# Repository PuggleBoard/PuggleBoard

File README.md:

PuggleBoard
===

Note: The PuggleBoard project is no longer under active development as of 06/2016. For alternative low-cost electrophysiology options, please see <a href="http://github.com/rtxi/rtxi">RTXI</a> or <a href="http://github.com/open-ephys/">Open-Ephys</a>.

The [PuggleBoard] (http://puggleboard.com/) is an I/O interface that plugs into the BeagleBone Black's expansion headers and is controlled by <a href="https://github.com/PuggleBoard/PuggleDriver">PuggleDriver</a>.

To get started, please refer to the <a href="https://github.com/PuggleBoard/PuggleBoard/wiki">wiki</a>. If you encounter any trouble or have any questions, post them to the <a href="https://github.com/PuggleBoard/PuggleBoard/issues">issues section</a> and we'll help get you started.

Visit visit the <a href="http://puggleboard.com">Puggleboard</a> site for more information on Puggle and it's hardware/software components.

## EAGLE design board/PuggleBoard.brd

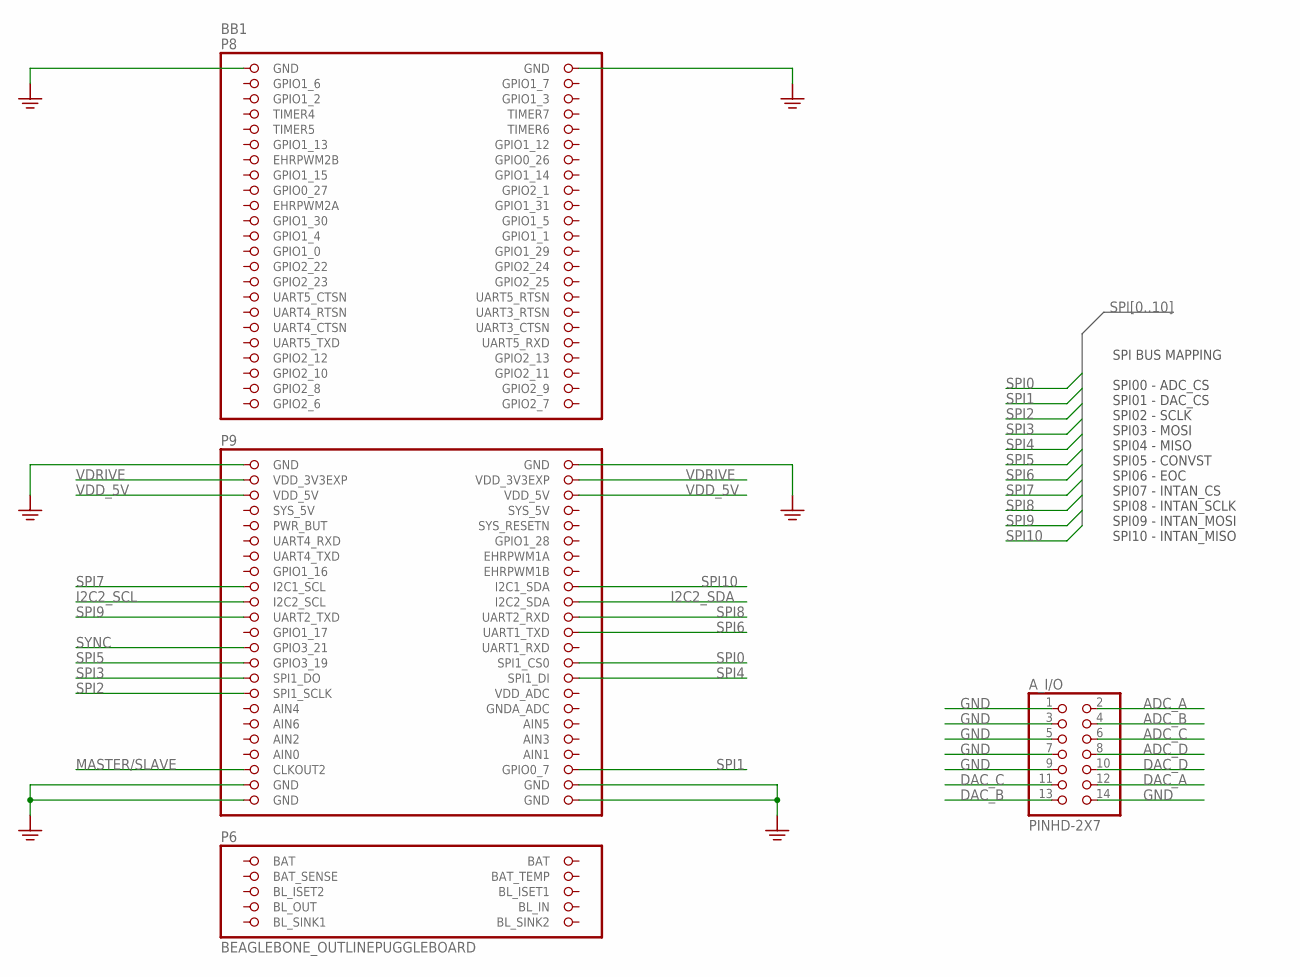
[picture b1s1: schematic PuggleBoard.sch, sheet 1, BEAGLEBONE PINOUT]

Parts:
A_I/O: PINHD-2X7; 2X07
BB1: BEAGLEBONE_OUTLINEPUGGLEBOARD; PUGGLEBOARD_SHIELD

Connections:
ADC_A: A_I/O.2; also elsewhere on the board
ADC_B: A_I/O.4; also elsewhere on the board
ADC_C: A_I/O.6; also elsewhere on the board
ADC_D: A_I/O.8; also elsewhere on the board
BAT_SENSE: BB1.95 (BAT_SENSE)
BL_IN: BB1.97 (BL_IN)
BL_OUT: BB1.100 (BL_OUT)
BL_SINK1: BB1.101 (BL_SINK1)
BL_SINK2: BB1.102 (BL_SINK2)
DAC_A: A_I/O.12; also elsewhere on the board
DAC_B: A_I/O.13; also elsewhere on the board
DAC_C: A_I/O.11; also elsewhere on the board
DAC_D: A_I/O.10; also elsewhere on the board
GND: A_I/O.1, A_I/O.3, A_I/O.5, A_I/O.7, A_I/O.9, A_I/O.14, BB1.1 (GND), BB1.2 (GND), BB1.47 (GND), BB1.48 (GND), BB1.89 (GND), BB1.90 (GND), BB1.91 (GND), BB1.92 (GND); also elsewhere on the board
I2C2_SCL: BB1.65 (I2C2_SCL); also elsewhere on the board
I2C2_SDA: BB1.66 (I2C2_SDA); also elsewhere on the board
MASTER/SLAVE: BB1.87 (CLKOUT2); also elsewhere on the board
SPI0: BB1.74 (SPI1_CS0); also elsewhere on the board
SPI1: BB1.88 (GPIO0_7); also elsewhere on the board
SPI2: BB1.77 (SPI1_SCLK); also elsewhere on the board
SPI3: BB1.75 (SPI1_DO); also elsewhere on the board
SPI4: BB1.76 (SPI1_DI); also elsewhere on the board
SPI5: BB1.73 (GPIO3_19); also elsewhere on the board
SPI6: BB1.70 (UART1_TXD); also elsewhere on the board
SPI7: BB1.63 (I2C1_SCL); also elsewhere on the board
SPI8: BB1.68 (UART2_RXD); also elsewhere on the board
SPI9: BB1.67 (UART2_TXD); also elsewhere on the board
SPI10: BB1.64 (I2C1_SDA); also elsewhere on the board
SYNC: BB1.71 (GPIO3_21); also elsewhere on the board
VDD_5V: BB1.51 (VDD_5V), BB1.52 (VDD_5V); also elsewhere on the board
VDRIVE: BB1.49 (VDD_3V3EXP), BB1.50 (VDD_3V3EXP); also elsewhere on the board

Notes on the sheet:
SPI BUS MAPPING SPI00 - ADC_CS SPI01 - DAC_CS SPI02 - SCLK SPI03 - MOSI SPI04 - MISO SPI05 - CONVST SPI06 - EOC SPI07 - INTAN_CS SPI08 - INTAN_SCLK SPI09 - INTAN_MOSI SPI10 - INTAN_MISO

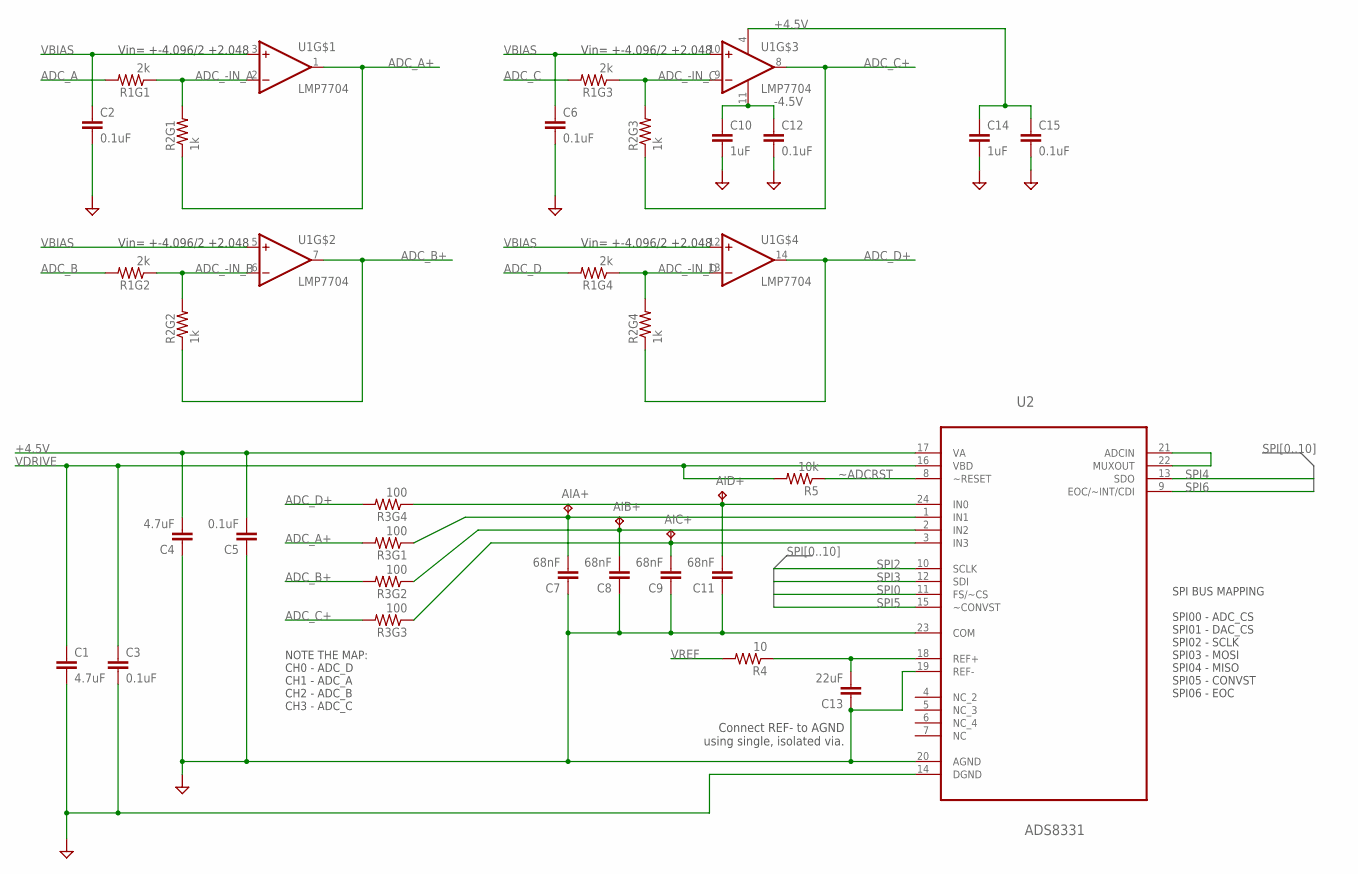
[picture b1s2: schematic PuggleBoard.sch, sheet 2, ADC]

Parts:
AIA+: TPB1,27; B1,27
AIB+: TPB1,27; B1,27
AIC+: TPB1,27; B1,27
AID+: TPB1,27; B1,27
C1, C4: 4.7uF; 0603
C2, C3, C5, C6, C12, C15: 0.1uF; 0603
C7, C8, C9, C11: 68nF; 0603
C10, C14: 1uF; 0603
C13: 22uF; 0805
R1: 2k; RX4_0612
R2: 1k; RX4_0612
R3: 100; RX4_0612
R4: 10; 0603
R5: 10k; 0603
U1: LMP7704; SOP65P640X120-14N-MOD
U2: ADS8331; SOP65P640X120-24N

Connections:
+4.5V: C4.2, C5.2, C14.1, C15.1, U1.4 (V+), U2.17 (VA); also elsewhere on the board
-4.5V: C10.1, C12.1, U1.11 (V-); also elsewhere on the board
ADC_-IN_A: R1.P1 (1), R2.P2 (2), U1.2 (-IN)
ADC_-IN_B: R1.P3 (1), R2.P4 (2), U1.6 (-IN)
ADC_-IN_C: R1.P5 (1), R2.P6 (2), U1.9 (-IN)
ADC_-IN_D: R1.P7 (1), R2.P8 (2), U1.13 (-IN)
ADC_A: R1.P2 (2); also elsewhere on the board
ADC_A+: R2.P1 (1), R3.P2 (2), U1.1 (OUT)
ADC_B: R1.P4 (2); also elsewhere on the board
ADC_B+: R2.P3 (1), R3.P4 (2), U1.7 (OUT)
ADC_C: R1.P6 (2); also elsewhere on the board
ADC_C+: R2.P5 (1), R3.P6 (2), U1.8 (OUT)
ADC_D: R1.P8 (2); also elsewhere on the board
ADC_D+: R2.P7 (1), R3.P8 (2), U1.14 (OUT)
GND: C1.2, C2.2, C3.2, C4.1, C5.1, C6.2, C7.1, C8.1, C9.1, C10.2, C11.1, C12.2, C13.1, C14.2, C15.2, U2.14 (DGND), U2.19 (REF-), U2.20 (AGND), U2.23 (COM); also elsewhere on the board
unnamed: U2.21 (ADCIN), U2.22 (MUXOUT)
unnamed: C13.2, R4.1, U2.18 (REF+)
unnamed: AIA+.TP, C7.2, R3.P1 (1), U2.1 (IN1)
unnamed: AIB+.TP, C8.2, R3.P3 (1), U2.2 (IN2)
unnamed: AIC+.TP, C9.2, R3.P5 (1), U2.3 (IN3)
unnamed: AID+.TP, C11.2, R3.P7 (1), U2.24 (IN0)
SPI0: U2.11 (FS/~CS); also elsewhere on the board
SPI2: U2.10 (SCLK); also elsewhere on the board
SPI3: U2.12 (SDI); also elsewhere on the board
SPI4: U2.13 (SDO); also elsewhere on the board
SPI5: U2.15 (~CONVST); also elsewhere on the board
SPI6: U2.9 (EOC/~INT/CDI); also elsewhere on the board
VBIAS: C2.1, C6.1, U1.3 (+IN), U1.5 (+IN), U1.10 (+IN), U1.12 (+IN); also elsewhere on the board
VDRIVE: C1.1, C3.1, R5.2, U2.16 (VBD); also elsewhere on the board
VREF: R4.2; also elsewhere on the board
~ADCRST: R5.1, U2.8 (~RESET)

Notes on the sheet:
Connect REF- to AGND using single, isolated via.
Vin= +-4.096/2 +2.048
SPI BUS MAPPING SPI00 - ADC_CS SPI01 - DAC_CS SPI02 - SCLK SPI03 - MOSI SPI04 - MISO SPI05 - CONVST SPI06 - EOC
NOTE THE MAP: CH0 - ADC_D CH1 - ADC_A CH2 - ADC_B CH3 - ADC_C

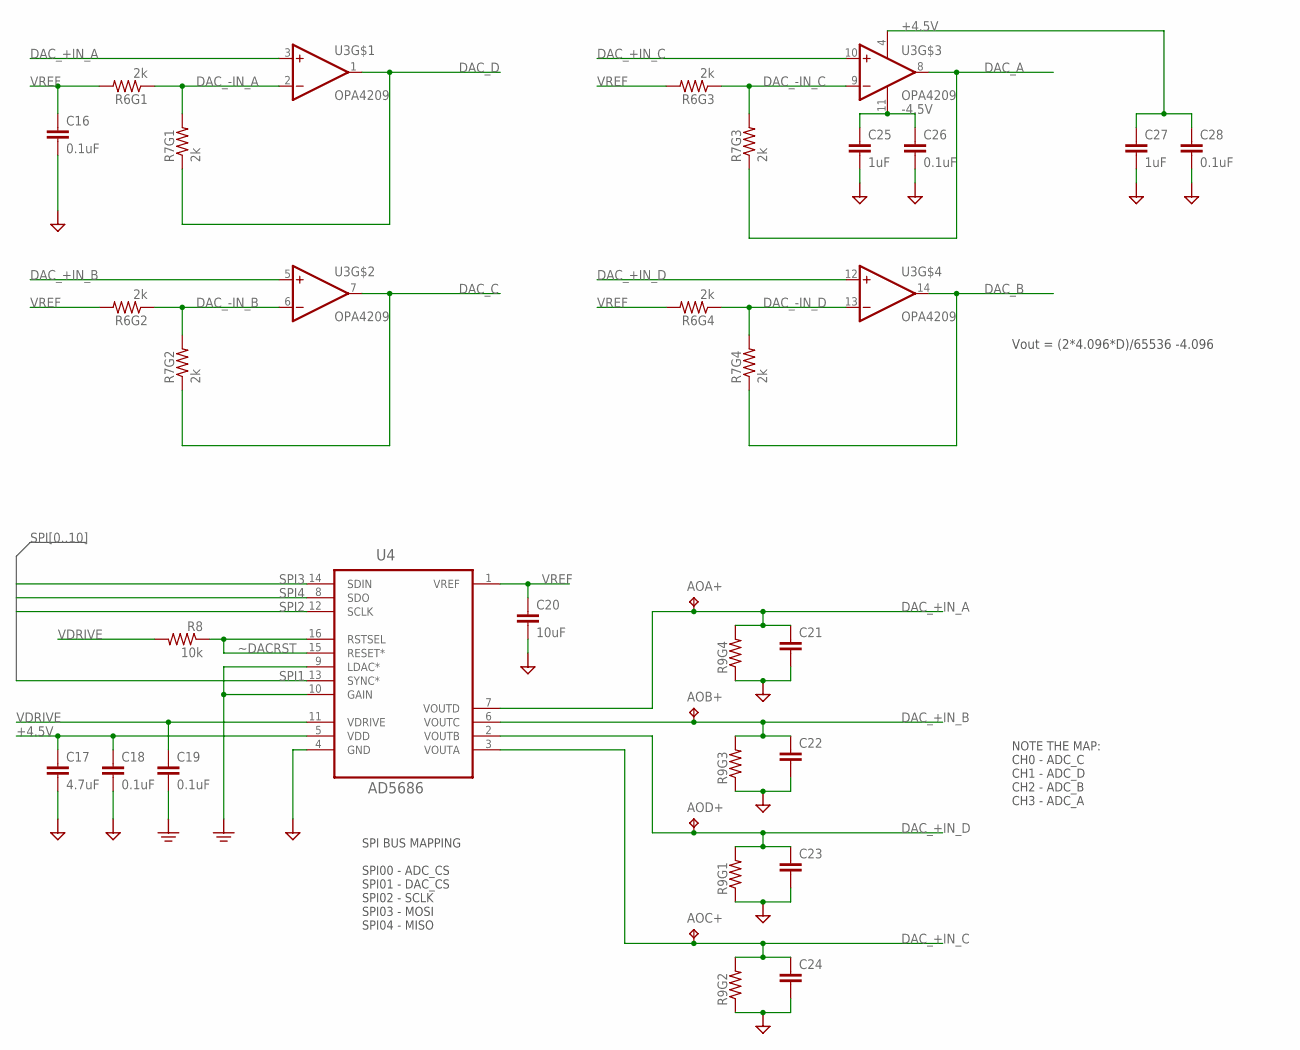
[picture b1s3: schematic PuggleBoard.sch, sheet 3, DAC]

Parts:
AOA+: TPB1,27; B1,27
AOB+: TPB1,27; B1,27
AOC+: TPB1,27; B1,27
AOD+: TPB1,27; B1,27
C16, C18, C19, C26, C28: 0.1uF; 0603
C17: 4.7uF; 0603
C20: 10uF; 0805
C21, C22, C23, C24: C_0603; 0603
C25, C27: 1uF; 0603
R6, R7: 2k; RX4_0612
R8: 10k; 0603
R9: RX4_0612
U3: OPA4209; SOP65P640X120-14N-MOD
U4: AD5686; MO-153-AB

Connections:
+4.5V: C17.1, C18.1, C27.1, C28.1, U3.4 (V+), U4.5 (VDD); also elsewhere on the board
-4.5V: C25.1, C26.1, U3.11 (V-); also elsewhere on the board
DAC_+IN_A: AOA+.TP, C21.1, R9.P8 (2), U3.3 (+IN), U4.7 (VOUTD)
DAC_+IN_B: AOB+.TP, C22.1, R9.P6 (2), U3.5 (+IN), U4.6 (VOUTC)
DAC_+IN_C: AOC+.TP, C24.1, R9.P4 (2), U3.10 (+IN), U4.3 (VOUTA)
DAC_+IN_D: AOD+.TP, C23.1, R9.P2 (2), U3.12 (+IN), U4.2 (VOUTB)
DAC_-IN_A: R6.P1 (1), R7.P2 (2), U3.2 (-IN)
DAC_-IN_B: R6.P3 (1), R7.P4 (2), U3.6 (-IN)
DAC_-IN_C: R6.P5 (1), R7.P6 (2), U3.9 (-IN)
DAC_-IN_D: R6.P7 (1), R7.P8 (2), U3.13 (-IN)
DAC_A: R7.P5 (1), U3.8 (OUT); also elsewhere on the board
DAC_B: R7.P7 (1), U3.14 (OUT); also elsewhere on the board
DAC_C: R7.P3 (1), U3.7 (OUT); also elsewhere on the board
DAC_D: R7.P1 (1), U3.1 (OUT); also elsewhere on the board
GND: C16.2, C17.2, C18.2, C19.2, C20.2, C21.2, C22.2, C23.2, C24.2, C25.2, C26.2, C27.2, C28.2, R9.P1 (1), R9.P3 (1), R9.P5 (1), R9.P7 (1), U4.4 (GND), U4.9 (LDAC*), U4.10 (GAIN); also elsewhere on the board
SPI1: U4.13 (SYNC*); also elsewhere on the board
SPI2: U4.12 (SCLK); also elsewhere on the board
SPI3: U4.14 (SDIN); also elsewhere on the board
SPI4: U4.8 (SDO); also elsewhere on the board
VDRIVE: C19.1, R8.2, U4.11 (VDRIVE); also elsewhere on the board
VREF: C16.1, C20.1, R6.P2 (2), R6.P4 (2), R6.P6 (2), R6.P8 (2), U4.1 (VREF); also elsewhere on the board
~DACRST: R8.1, U4.15 (RESET*), U4.16 (RSTSEL)

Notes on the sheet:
Vout = (2*4.096*D)/65536 -4.096
SPI BUS MAPPING SPI00 - ADC_CS SPI01 - DAC_CS SPI02 - SCLK SPI03 - MOSI SPI04 - MISO
NOTE THE MAP: CH0 - ADC_C CH1 - ADC_D CH2 - ADC_B CH3 - ADC_A

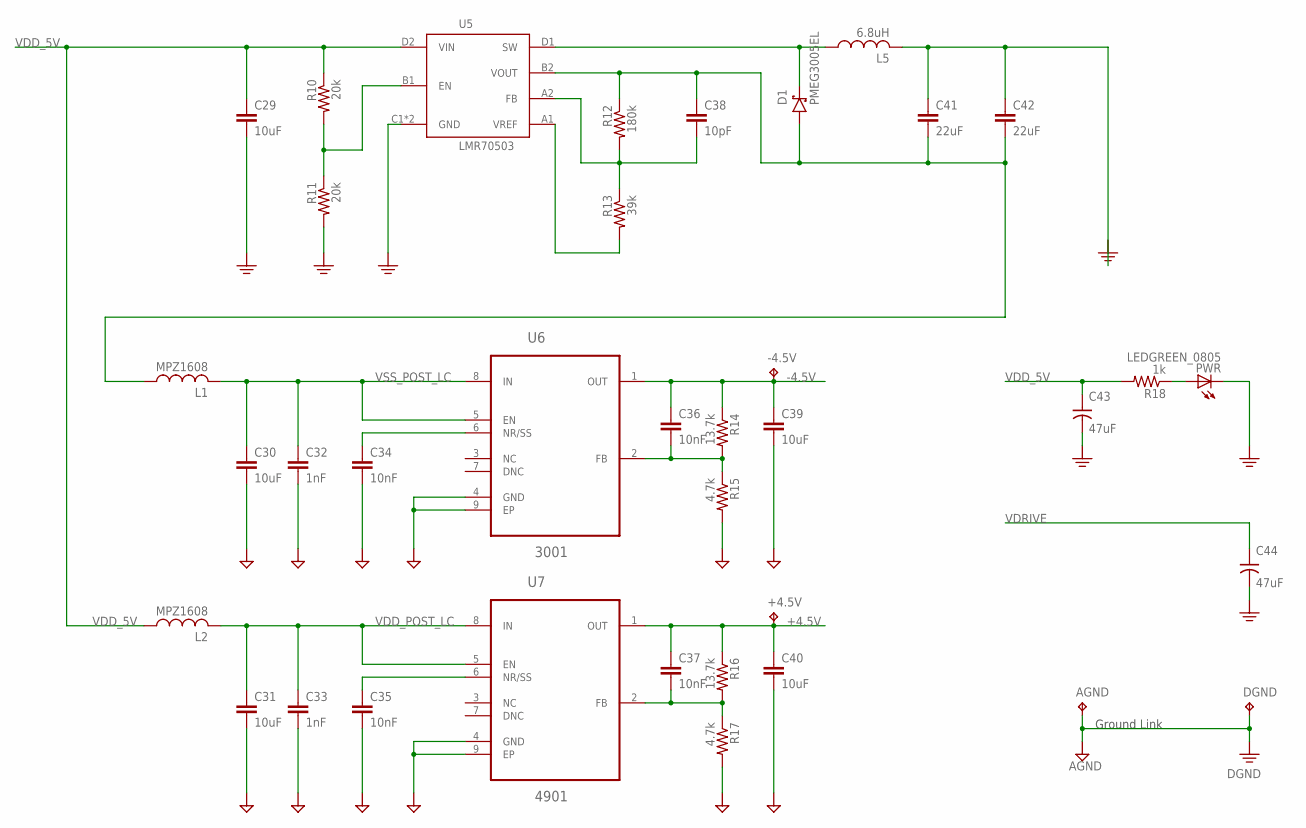
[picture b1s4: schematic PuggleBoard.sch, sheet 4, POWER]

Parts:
+4.5V: TPPAD1-17; P1-17
-4.5V: TPPAD1-17; P1-17
AGND: TPPAD1-17; P1-17
C29: 10uF; 0603
C30, C31, C39, C40: 10uF; 1206
C32, C33: 1nF; 0603
C34, C35, C36, C37: 10nF; 0603
C38: 10pF; 0402
C41, C42: 22uF; 0603
C43, C44: 47uF; 153CLV-0807
D1: PMEG3005EL; SOD882
DGND: TPPAD1-17; P1-17
L1, L2: MPZ1608; 0603
L5: 6.8uH; VLS2012E
PWR: LEDGREEN_0805; CHIP-LED0805
R10, R11: 20k; 0402
R12: 180k; 0402
R13: 39k; 0402
R14, R16: 13.7k; 0603
R15, R17: 4.7k; 0603
R18: 1k; 0603
U5: LMR70503; 8BGA
U6: 3001; SOP65P490X110-9N
U7: 4901; SOP65P490X110-9N

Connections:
+4.5V: +4.5V.TP, C37.1, C40.1, R16.1, U7.1 (OUT); also elsewhere on the board
-4.5V: -4.5V.TP, C36.1, C39.1, R14.1, U6.1 (OUT); also elsewhere on the board
AGND1: C37.2, R16.2, R17.1, U7.2 (FB)
AGND2: C36.2, R14.2, R15.1, U6.2 (FB)
GND: AGND.TP, C29.2, C30.2, C31.2, C32.2, C33.2, C34.2, C35.2, C39.2, C40.2, C41.1, C42.1, C43.-, C44.-, DGND.TP, L5.2, PWR.C, R11.2, R15.2, R17.2, U5.C1 (GND), U5.C2 (GND), U6.4 (GND), U6.9 (EP), U7.4 (GND), U7.9 (EP); also elsewhere on the board
unnamed: C35.1, U7.6 (NR/SS)
unnamed: C34.1, U6.6 (NR/SS)
unnamed: R10.2, R11.1, U5.B1 (EN)
unnamed: C38.2, R12.2, R13.1, U5.A2 (FB)
unnamed: PWR.A, R18.1
unnamed: R13.2, U5.A1 (VREF)
SW: D1.C, L5.1, U5.D1 (SW)
VDD_5V: C29.1, C43.+, L2.1, R10.1, R18.2, U5.D2 (VIN); also elsewhere on the board
VDD_POST_LC: C31.1, C33.1, L2.2, U7.5 (EN), U7.8 (IN)
VDRIVE: C44.+; also elsewhere on the board
VOUT-: C38.1, C41.2, C42.2, D1.A, L1.1, R12.1, U5.B2 (VOUT)
VSS_POST_LC: C30.1, C32.1, L1.2, U6.5 (EN), U6.8 (IN)

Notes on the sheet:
Ground Link

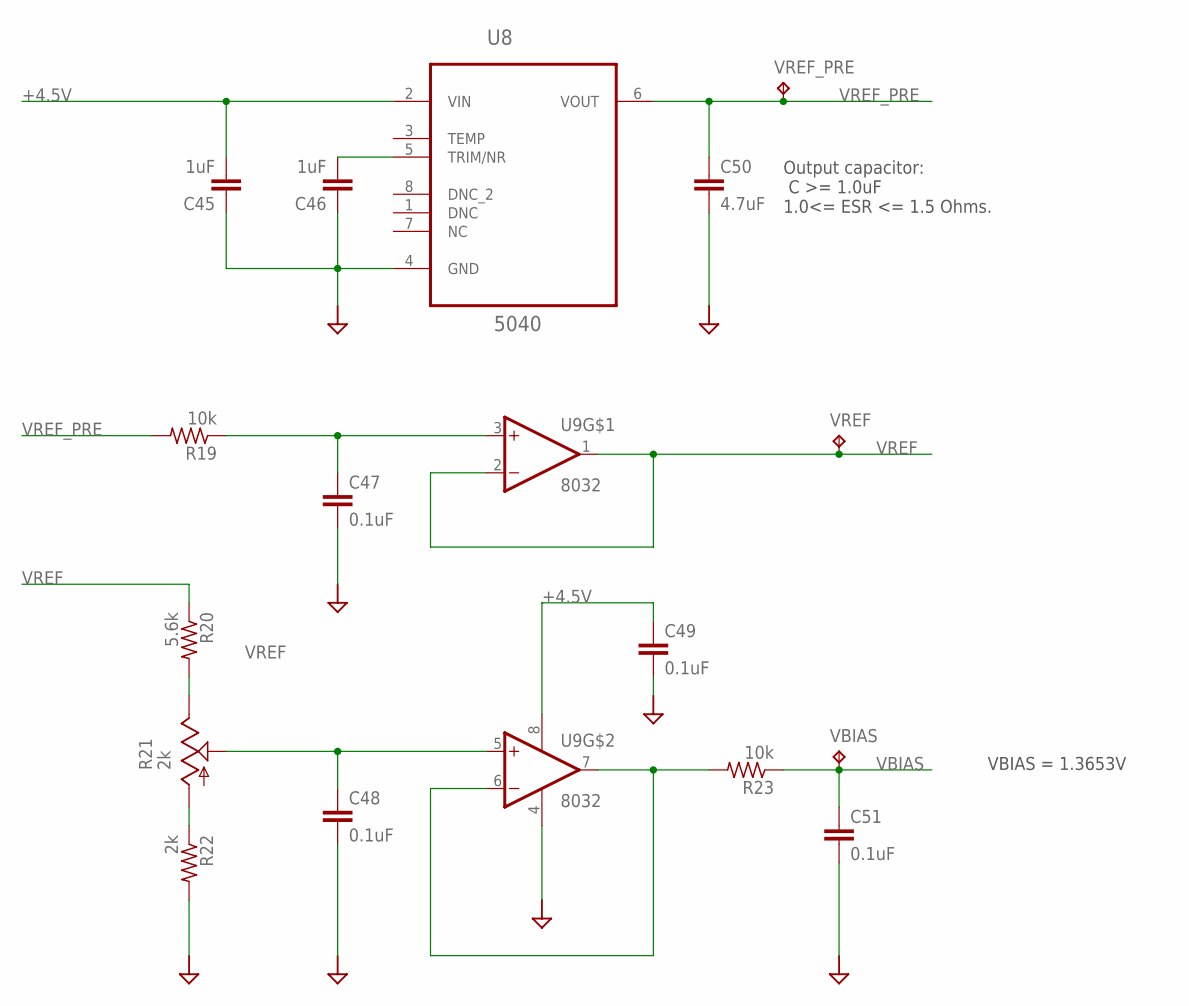
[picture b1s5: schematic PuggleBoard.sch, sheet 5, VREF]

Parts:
C45, C46: 1uF; 0603
C47, C48, C49, C51: 0.1uF; 0603
C50: 4.7uF; 1206
R19, R23: 10k; 0603
R20: 5.6k; 0603
R21: 2k; SM-42/43W
R22: 2k; 0603
U8: 5040; SOP65P490X110-8N
U9: 8032; SOP65P490X110-8N
VBIAS: TPB1,27; B1,27
VREF: TPB1,27; B1,27
VREF_PRE: TPB1,27; B1,27

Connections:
+4.5V: C45.2, C49.1, U8.2 (VIN), U9.8 (V+); also elsewhere on the board
GND: C45.1, C46.1, C47.2, C48.2, C49.2, C50.2, C51.2, R22.2, U8.4 (GND), U9.4 (V-); also elsewhere on the board
unnamed: C48.1, R21.2 (S), U9.5 (+IN)
unnamed: R21.1 (A), R22.1
unnamed: R23.2, U9.6 (-IN), U9.7 (OUT)
unnamed: R20.2, R21.3 (E)
unnamed: C47.1, R19.1, U9.3 (+IN)
unnamed: C46.2, U8.5 (TRIM/NR)
VBIAS: C51.1, R23.1, VBIAS.TP; also elsewhere on the board
VREF: R20.1, U9.1 (OUT), U9.2 (-IN), VREF.TP; also elsewhere on the board
VREF_PRE: C50.1, R19.2, U8.6 (VOUT), VREF_PRE.TP

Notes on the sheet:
Output capacitor: C >= 1.0uF 1.0<= ESR <= 1.5 Ohms.
VBIAS = 1.3653V

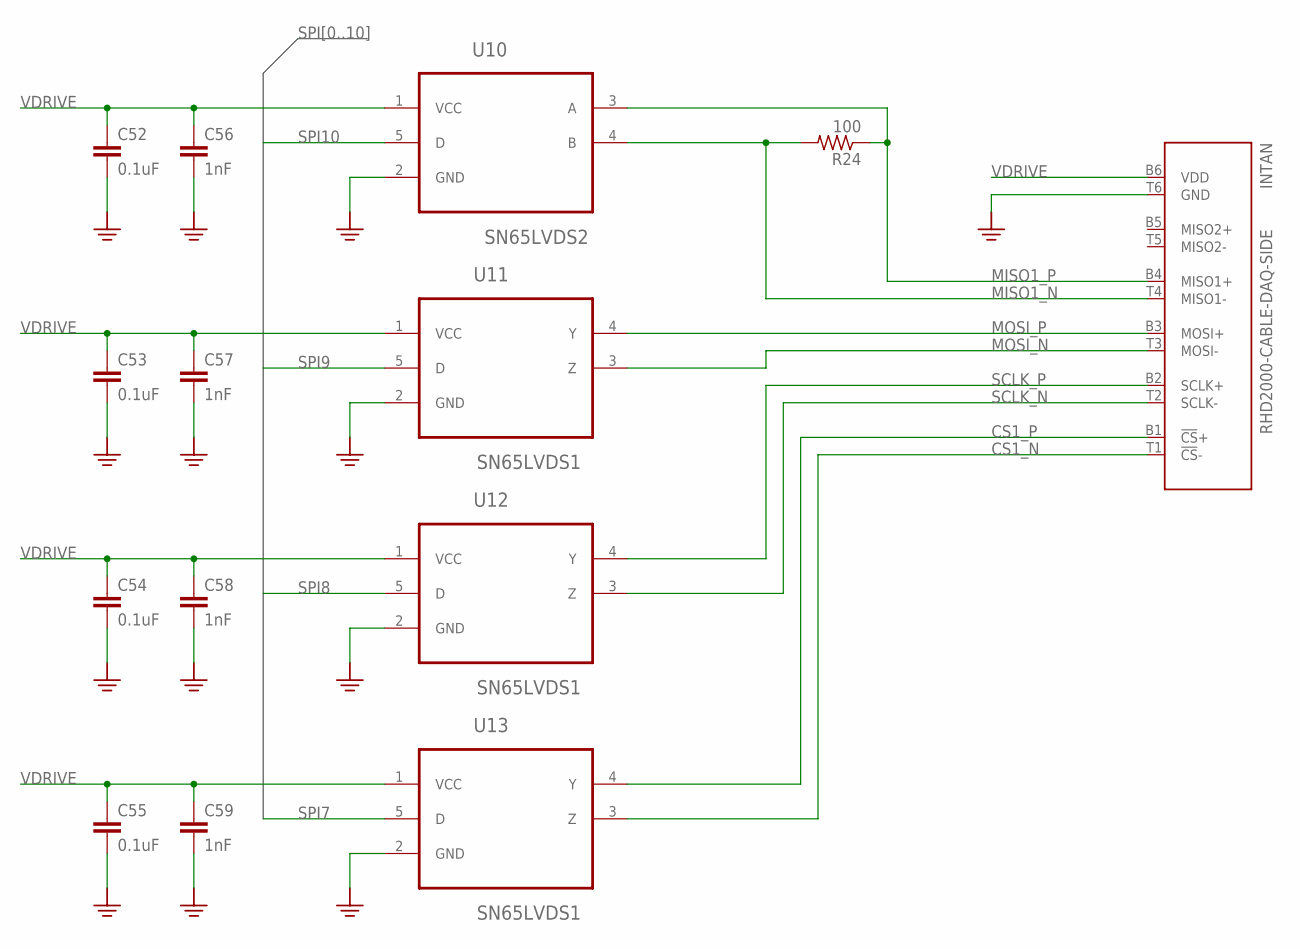
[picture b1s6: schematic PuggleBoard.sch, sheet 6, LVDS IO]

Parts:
C52, C53, C54, C55: 0.1uF; 0603
C56, C57, C58, C59: 1nF; 0603
INTAN: RHD2000-CABLE-DAQ-SIDE; OMNETICS_PZN-12-AA
R24: 100; 0603
U10: SN65LVDS2; SOT95P280X145-5N; DIGIKEY 296-6920-1-ND
U11, U12, U13: SN65LVDS1; SOT95P280X145-5N; DIGIKEY 296-6919-1-ND

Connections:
CS1_N: INTAN.T1 (!CS!-), U13.3 (Z)
CS1_P: INTAN.B1 (!CS!+), U13.4 (Y)
GND: C52.2, C53.2, C54.2, C55.2, C56.2, C57.2, C58.2, C59.2, INTAN.T6 (GND), U10.2 (GND), U11.2 (GND), U12.2 (GND), U13.2 (GND); also elsewhere on the board
MISO1_N: INTAN.T4 (MISO1-), R24.2, U10.4 (B)
MISO1_P: INTAN.B4 (MISO1+), R24.1, U10.3 (A)
MOSI_N: INTAN.T3 (MOSI-), U11.3 (Z)
MOSI_P: INTAN.B3 (MOSI+), U11.4 (Y)
SCLK_N: INTAN.T2 (SCLK-), U12.3 (Z)
SCLK_P: INTAN.B2 (SCLK+), U12.4 (Y)
SPI7: U13.5 (D); also elsewhere on the board
SPI8: U12.5 (D); also elsewhere on the board
SPI9: U11.5 (D); also elsewhere on the board
SPI10: U10.5 (D); also elsewhere on the board
VDRIVE: C52.1, C53.1, C54.1, C55.1, C56.1, C57.1, C58.1, C59.1, INTAN.B6 (VDD), U10.1 (VCC), U11.1 (VCC), U12.1 (VCC), U13.1 (VCC); also elsewhere on the board

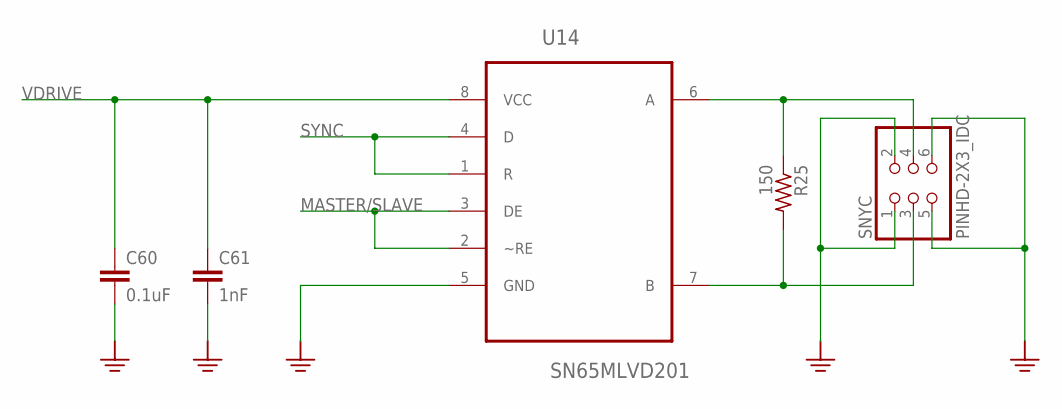
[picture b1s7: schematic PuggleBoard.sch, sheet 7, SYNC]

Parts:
C60: 0.1uF; 0603
C61: 1nF; 0603
R25: 150; 0603
SNYC: PINHD-2X3_IDC; 2X03_IDC
U14: SN65MLVD201; SOIC127P600X175-8N

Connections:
GND: C60.2, C61.2, SNYC.1, SNYC.2, SNYC.5, SNYC.6, U14.5 (GND); also elsewhere on the board
MASTER/SLAVE: U14.2 (~RE), U14.3 (DE); also elsewhere on the board
SYNC: U14.1 (R), U14.4 (D); also elsewhere on the board
SYNC_N: R25.2, SNYC.3, U14.7 (B)
SYNC_P: R25.1, SNYC.4, U14.6 (A)
VDRIVE: C60.1, C61.1, U14.8 (VCC); also elsewhere on the board

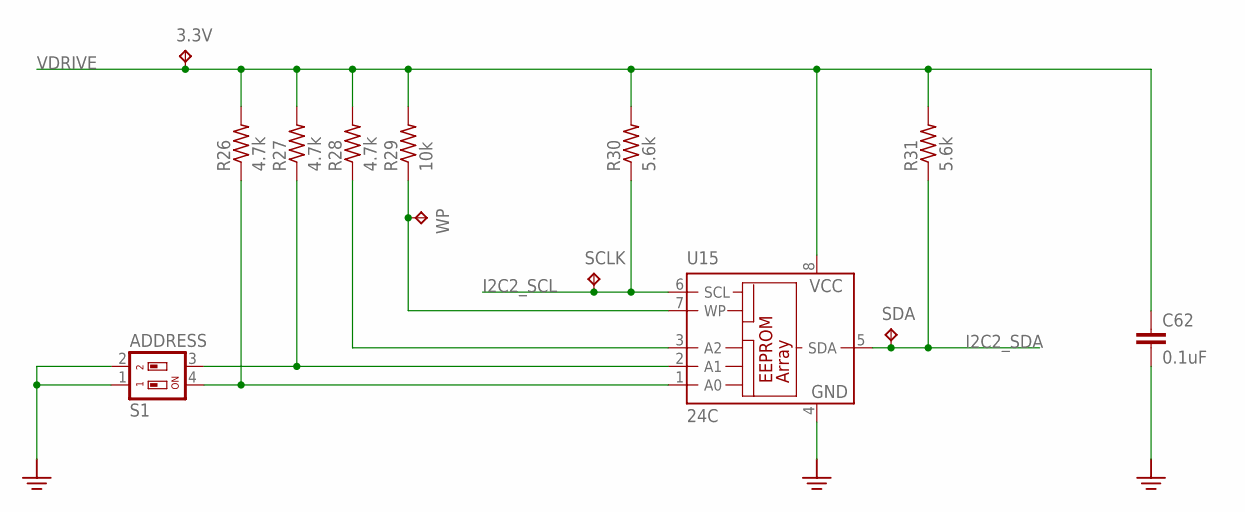
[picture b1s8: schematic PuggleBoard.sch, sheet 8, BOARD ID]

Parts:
3.3V: TPPAD1-17; P1-17
C62: 0.1uF; 0603
R26, R27, R28: 4.7k; 0603
R29: 10k; 0603
R30, R31: 5.6k; 0603
S1: ADDRESS; SMS-002
SCLK: TPB1,27; B1,27
SDA: TPB1,27; B1,27
U15: 24C; SO-08
WP: TPTP14SQ; TP14SQ

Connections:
GND: C62.2, S1.1, S1.2, U15.4 (GND); also elsewhere on the board
I2C2_SCL: R30.1, SCLK.TP, U15.6 (SCL); also elsewhere on the board
I2C2_SDA: R31.1, SDA.TP, U15.5 (SDA); also elsewhere on the board
unnamed: R26.1, S1.4, U15.1 (A0)
unnamed: R27.1, S1.3, U15.2 (A1)
unnamed: R28.1, U15.3 (A2)
unnamed: R29.1, U15.7 (WP), WP.TP
VDRIVE: 3.3V.TP, C62.1, R26.2, R27.2, R28.2, R29.2, R30.2, R31.2, U15.8 (VCC); also elsewhere on the board

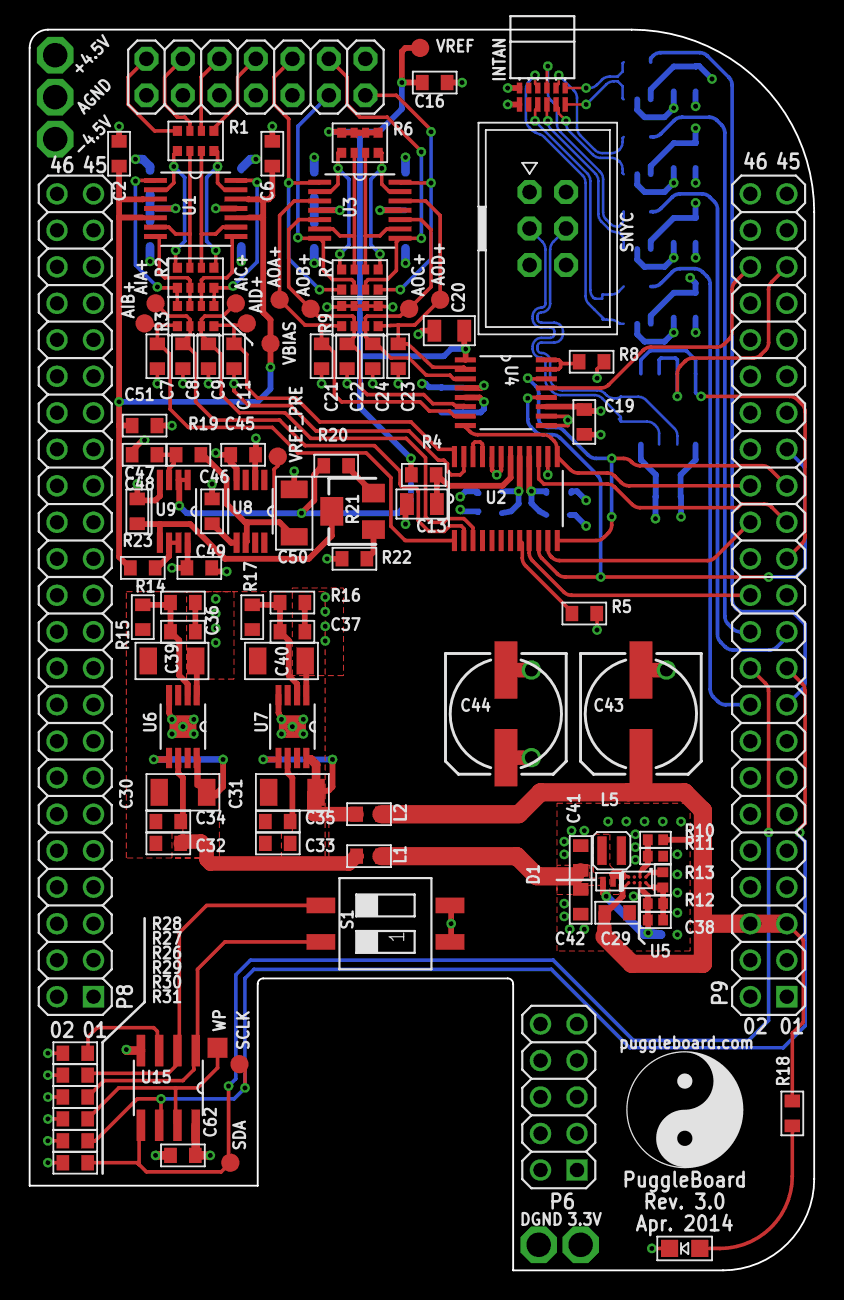
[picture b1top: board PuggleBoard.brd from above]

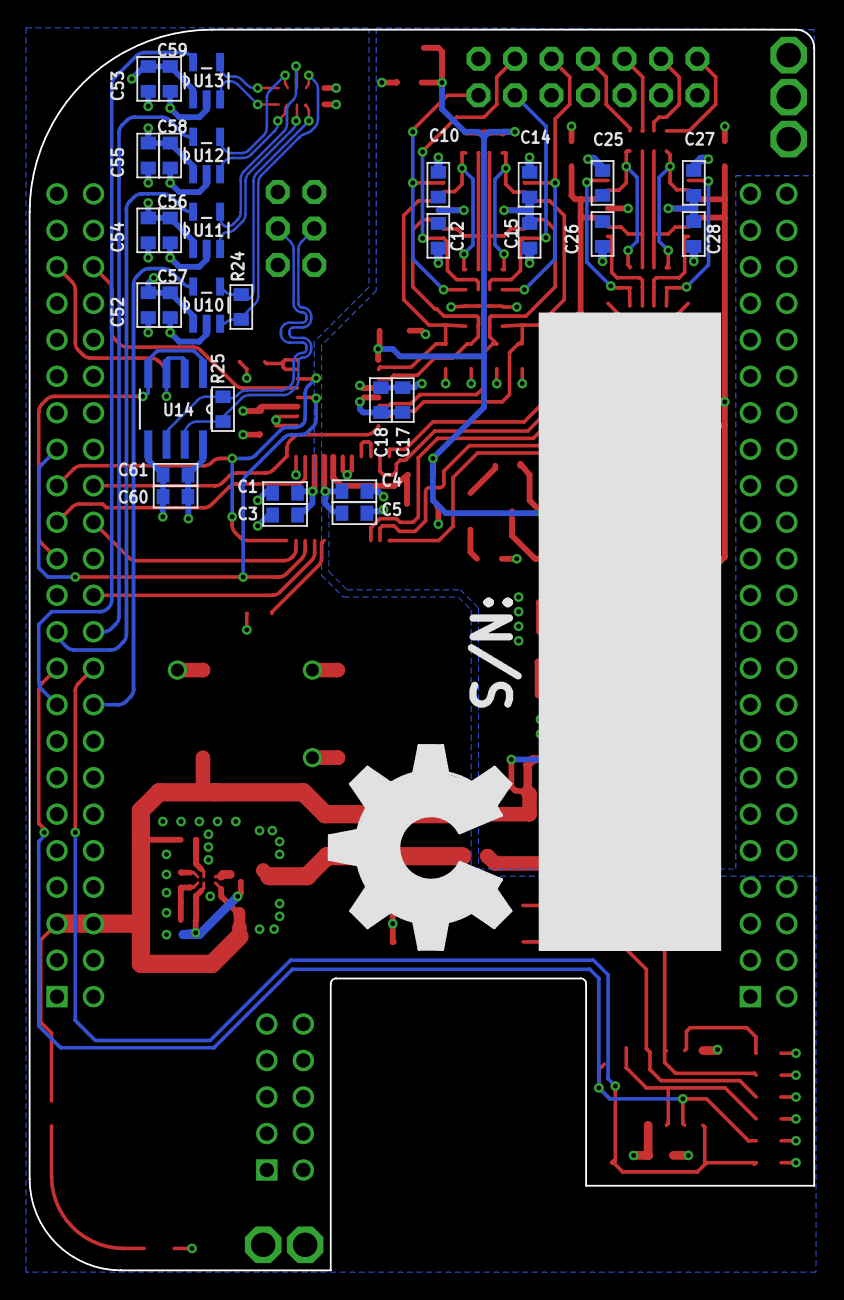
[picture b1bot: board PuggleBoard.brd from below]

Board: 4 copper layers, 54.6 x 86.4 mm, 139 parts (32 on the bottom side), 87 nets.

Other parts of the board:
U$1: PB-LOGO-NOSITE
U$2: OSHW_FILLX500_NOTEXT

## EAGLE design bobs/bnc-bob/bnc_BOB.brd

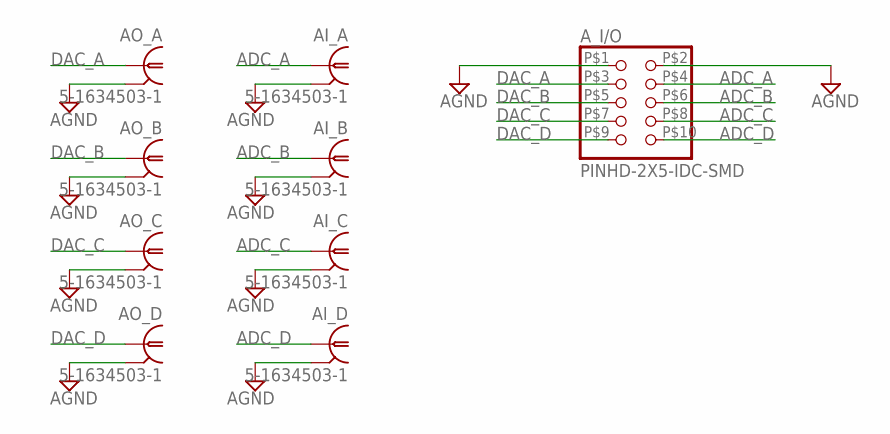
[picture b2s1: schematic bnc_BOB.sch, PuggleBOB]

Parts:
AI_A: 5-1634503-1; B35N61
AI_B: 5-1634503-1; B35N61
AI_C: 5-1634503-1; B35N61
AI_D: 5-1634503-1; B35N61
AO_A: 5-1634503-1; B35N61
AO_B: 5-1634503-1; B35N61
AO_C: 5-1634503-1; B35N61
AO_D: 5-1634503-1; B35N61
A_I/O: PINHD-2X5-IDC-SMD; 2X05-IDC-SMD

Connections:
ADC_A: AI_A.1, A_I/O.P$4 (4)
ADC_B: AI_B.1, A_I/O.P$6 (6)
ADC_C: AI_C.1, A_I/O.P$8 (8)
ADC_D: AI_D.1, A_I/O.P$10 (10)
AGND: AI_A.2, AI_A.3 (2), AI_A.4 (2), AI_A.5 (2), AI_B.2, AI_B.3 (2), AI_B.4 (2), AI_B.5 (2), AI_C.2, AI_C.3 (2), AI_C.4 (2), AI_C.5 (2), AI_D.2, AI_D.3 (2), AI_D.4 (2), AI_D.5 (2), AO_A.2, AO_A.3 (2), AO_A.4 (2), AO_A.5 (2), AO_B.2, AO_B.3 (2), AO_B.4 (2), AO_B.5 (2), AO_C.2, AO_C.3 (2), AO_C.4 (2), AO_C.5 (2), AO_D.2, AO_D.3 (2), AO_D.4 (2), AO_D.5 (2), A_I/O.P$1 (1), A_I/O.P$2 (2)
DAC_A: AO_A.1, A_I/O.P$3 (3)
DAC_B: AO_B.1, A_I/O.P$5 (5)
DAC_C: AO_C.1, A_I/O.P$7 (7)
DAC_D: AO_D.1, A_I/O.P$9 (9)

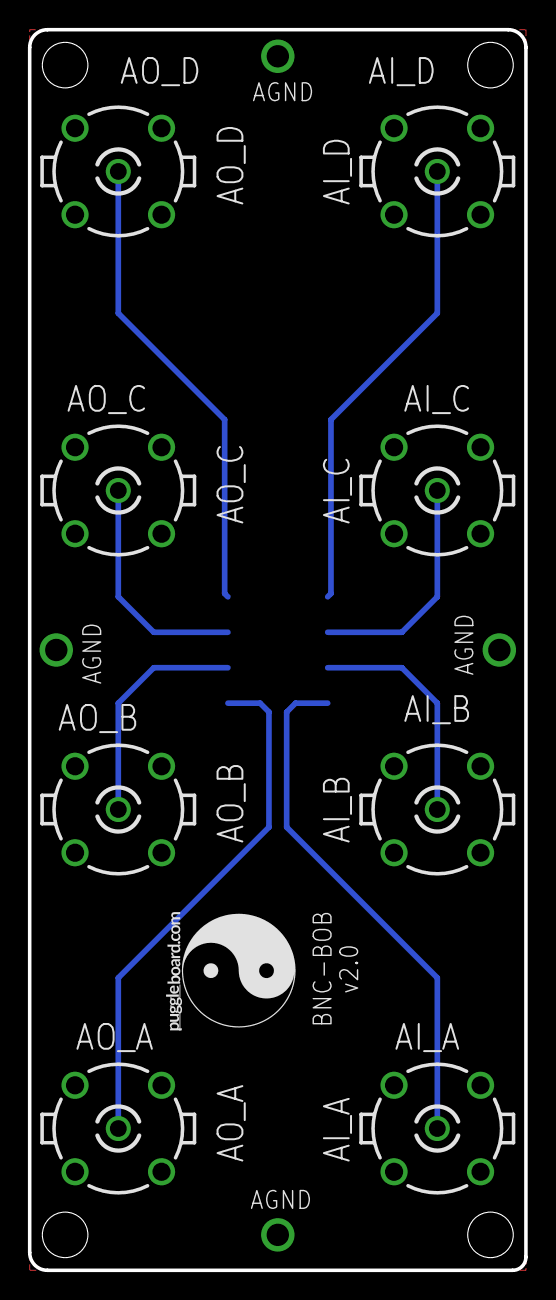
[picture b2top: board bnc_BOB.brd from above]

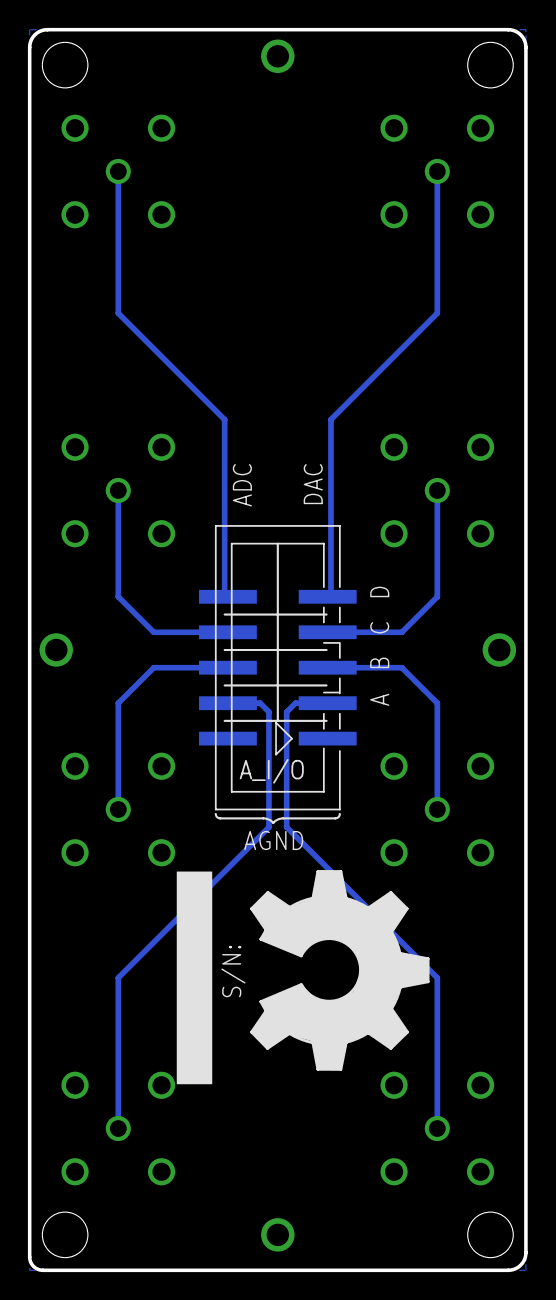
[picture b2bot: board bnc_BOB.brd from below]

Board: 2 copper layers, 35.6 x 88.9 mm, 11 parts (2 on the bottom side), 9 nets.

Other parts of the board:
U$1: PB-LOGO
U$2: OSHW_FILLX500_NOTEXT
